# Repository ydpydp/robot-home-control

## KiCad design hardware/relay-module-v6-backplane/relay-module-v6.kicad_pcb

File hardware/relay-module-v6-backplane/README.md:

# 继电器模块板 v6（Backplane 版）

与 `../relay-module-v6/` 同一设计，由 Backplane agent（Claude Code）在 Backplane 里修完的版本：GND 铺铜已填、J3/J8 丝印三角缩短 0.3mm，DRC 0 违规、0 未连接。

## 重要：这是单向门版本

- 本工程由 **Backplane 自带的 KiCad 分支版（10.99.0 开发版）**写出，PCB 文件格式 version 为 `20261031`。
- **正式 KiCad（9 / 10.0.8）打不开它**，会报“文件由更新版本创建”。用正式 KiCad 打开保存后也不能再回 Backplane 编辑。
- 想在正式 KiCad 里继续改，请用 `../relay-module-v6/`（KiCad 10.0.8 版，改动已手工搬回，DRC 同样清零）。
- 想继续在 Backplane 里改、看 3D view，就用本目录。

## 文件

- `relay-module-v6.kicad_pcb` / `.kicad_sch` / `.kicad_pro` / `.kicad_dru`：Backplane KiCad 10.99 工程
- `TerminalBlock_3.5mm.pretty/`：3.5mm 弯针拔插端子定制封装（孔 Ø1.40）
- `.backplane.json` / `.backplane/`：Backplane 项目文件（`intent.md`、`review.md`、`design-review.json` 为 agent 的设计复核记录；`.backplane/history.git` 为 Backplane 内部快照历史，未随附）
- BOM 与 Gerber 见 `../relay-module-v6/`（同一设计，共用）

## 规格与注意事项

见 `../relay-module-v6/README.md`（尺寸、电气、ULN2003 反相、NO/NC 核对、SMT 料号均相同）。

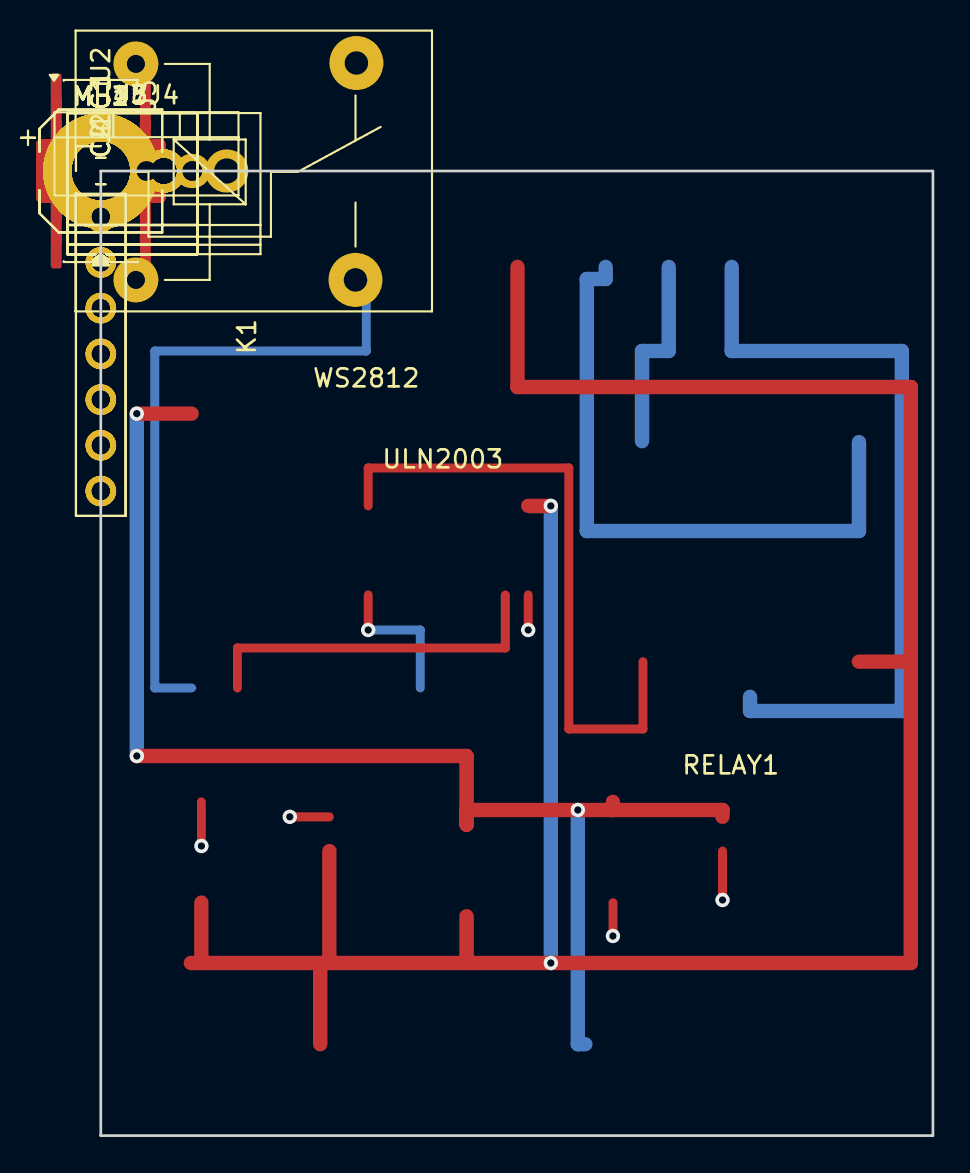
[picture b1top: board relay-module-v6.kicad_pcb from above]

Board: 2 copper layers, 46.2 x 53.6 mm, 18 parts (0 on the bottom side), 10 nets.

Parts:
C1, C3: CP_Elec_6.3x5.3
C2, C4: C_0805_2012Metric
J1, J2: PinHeader_1x08_P2.54mm_Vertical
J3, J5, J7, J8: TerminalBlock_3.5mm_1x02_P3.50mm_Horizontal_D1.4_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; TerminalBlock_3.5mm_1x02_P3.50mm_Horizontal_D1.4
J4: TerminalBlock_3.5mm_1x03_P3.50mm_Horizontal_D1.4_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; TerminalBlock_3.5mm_1x03_P3.50mm_Horizontal_D1.4
K1: Relay_SPDT_SANYOU_SRD_Series_Form_C
MH1, MH2, MH3, MH4: MountingHole_3.2mm_M3_Pad
U2: SOIC-16_3.9x9.9mm_P1.27mm
U3: TO-220-3_Vertical

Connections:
+5V: C3.1, C4.1, J1.1, J8.1, U3.3
+12V: C1.1, C2.1, J3.1, J7.1, K1.2, U2.9, U3.1
GND: C1.2, C2.2, C3.2, C4.2, J1.2, J3.2, J5.2, J7.2, J8.2, U2.8, U3.2
RELAY1_COM: J4.1, K1.1
RELAY1_IN: J2.6, U2.1
RELAY1_NC: J4.3, K1.3
RELAY1_NO: J4.2, K1.4
RELAY1_OUT: K1.5, U2.16
RELAY2_IN: J2.2, U2.7
WS2812_DIN: J2.1, J5.1

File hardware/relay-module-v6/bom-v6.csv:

Reference,Qty,Value,Description,Package/Footprint,Manufacturer PN (suggested),Notes
"J1,J2",2,Pin header 1x08,"Single-row pin header, 2.54mm pitch, vertical, through-hole; two headers form the 2x8 socket for the ESP32-C3 Super Mini (15.24mm row spacing)",PinHeader_1x08_P2.54mm_Vertical,Generic 2.54mm 1x08 header (female socket recommended),"Body ~20.3 x 2.54mm per header; 2.54mm pitch; use female socket headers so the Super Mini plugs in; J1 = 5V/GND/3V3/GPIO4/3/2/1/0, J2 = GPIO5/6/7/8/9/10/20/21 (per board silkscreen); v5 layout: headers horizontal, J1 upper, J2 lower, left side"
U2,1,ULN2003A,"7-channel Darlington transistor array, 50V / 500mA per channel, with integrated freewheeling diodes; INVERTS (GPIO high = relay ON)",SOIC-16_3.9x9.9mm_P1.27mm,ULN2003AD (TI) / ULN2003A (ST),"Body 3.9 x 9.9mm, 1.27mm pitch; v5 uses ONLY ch 1 (IN1/OUT1, pins 1/16) -> K1; ch 7 (IN7/OUT7, pins 7/10) unpopulated (relay 2 removed); pin 8 = GND, pin 9 = COM must connect to +12V so the kickback diodes can clamp relay coil flyback (12V relays since v3.4)"
K1,1,SRD-12VDC-SL-C,"12V SPDT relay (Form C), 10A / 250VAC contacts",Relay_SPDT_SANYOU_SRD_Series_Form_C,SRD-12VDC-SL-C (Songle),"Coil 12V, 400 ohm +/-10%, ~30mA (~360mW); contacts 10A 250VAC / 10A 30VDC; body ~19 x 15.5 x 15.5mm (verify against datasheet); NO/NC pin assignment must be verified with a multimeter before mains use (see notes); single relay in v5 (K2/J6 removed per user 2026-11-16)"
U3,1,7805 (5V 1A),"5V fixed linear voltage regulator, 1A",TO-220-3_Vertical,L7805CV (ST) / LM7805CT (TI),"TO-220; pinout 1=IN, 2=GND, 3=OUT; dropout ~2V (needs >= ~7V in for 5V out); feeds only the Super Mini + WS2812 (relay coil runs off 12V since v3.4); at ~150-250mA load from 12V it dissipates ~1-1.4W - no heatsink needed at this load, keep some airflow / copper around it"
"C1,C3",2,100uF 25V,"SMD aluminum electrolytic capacitor, 100uF, 25V",CP_Elec_6.3x5.3,Generic 100uF 25V SMD electrolytic (actual part 6.5x6.5mm base, 5.5mm high),"No 6.5x5.5 model in the KiCad library; CP_Elec_6.3x5.3 is the closest (pads identical to 6.3x5.4, centres +/-2.8mm); the 6.5mm can solders straight onto the 6.3 footprint, overhanging each pad edge by 0.1mm; C1 = 12V input filter, C3 = 5V output filter; POLARIZED - observe + marking, reversed polarity will damage the capacitor"
"C2,C4",2,100nF 50V,"Ceramic capacitor (MLCC, X7R), 100nF (0.1uF), 50V",C_0805_2012Metric,Generic 100nF 50V X7R 0805,"0805 (2.0 x 1.25mm); C2 = 12V bypass, C4 = 5V bypass; non-polarized; X7R dielectric or better"
J3,1,Terminal block 1x02 3.5mm,"2-pin right-angle pluggable terminal block, 3.5mm pitch, for 12V DC input",TerminalBlock_3.5mm_1x02_P3.50mm_Horizontal_D1.4,"3.5mm pitch right-angle pluggable PCB terminal block (0.8mm square pins, D1.4 holes)","3.5mm pitch; project-local footprint based on Phoenix PT-1,5-2-3.5-H with drill enlarged to 1.4mm per the part drawing; 12V DC input, observe + / - marking; v5: bottom edge, wire entry faces down"
J4,1,Terminal block 1x03 3.5mm,"3-pin right-angle pluggable terminal block, 3.5mm pitch, relay COM / NO / NC output",TerminalBlock_3.5mm_1x03_P3.50mm_Horizontal_D1.4,"3.5mm pitch right-angle pluggable PCB terminal block (0.8mm square pins, D1.4 holes)","3.5mm pitch; project-local footprint based on Phoenix PT-1,5-3-3.5-H with drill enlarged to 1.4mm per the part drawing; J4 = relay 1 output; pin order COM / NO / NC per board silkscreen - verify NO/NC with a multimeter before mains use; v5: top-right edge, wire entry faces up"
J5,1,Terminal block 1x02 3.5mm,"2-pin right-angle pluggable terminal block, 3.5mm pitch, WS2812 interface (DIN / GND); DIN driven from GPIO5; strips take their 5V separately from J8",TerminalBlock_3.5mm_1x02_P3.50mm_Horizontal_D1.4,"3.5mm pitch right-angle pluggable PCB terminal block (0.8mm square pins, D1.4 holes)","3.5mm pitch; project-local footprint based on Phoenix PT-1,5-2-3.5-H with drill enlarged to 1.4mm per the part drawing; v5: top edge, wire entry faces up"
J7,1,Terminal block 1x02 3.5mm,"2-pin right-angle pluggable terminal block, 3.5mm pitch, +12V power output (+12V / GND)",TerminalBlock_3.5mm_1x02_P3.50mm_Horizontal_D1.4,"3.5mm pitch right-angle pluggable PCB terminal block (0.8mm square pins, D1.4 holes)","3.5mm pitch; same footprint as J3; v5: top edge next to J5, wire entry faces up"
J8,1,Terminal block 1x02 3.5mm,"2-pin right-angle pluggable terminal block, 3.5mm pitch, +5V power output (+5V / GND)",TerminalBlock_3.5mm_1x02_P3.50mm_Horizontal_D1.4,"3.5mm pitch right-angle pluggable PCB terminal block (0.8mm square pins, D1.4 holes)","3.5mm pitch; same footprint as J3; v5: bottom edge next to J3, wire entry faces down; +5V comes from the 7805"
MH1-MH4,4,Mounting hole M3,"M3 mounting hole, 3.2mm diameter, plated",MountingHole_3.2mm_M3_Pad,"- (hardware, not a component)","3.2mm hole for M3 screw; use M3 screws + standoffs; keep-out around holes per footprint courtyard (no copper / traces within the courtyard); v6: 4 holes, one per corner: MH1 top-left, MH4 top-right, MH2 bottom-right, MH3 bottom-left (MH4 restored 2026-11-16; top edge J5/J7/J4 repacked to make room)"
